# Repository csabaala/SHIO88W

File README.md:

# SHIO88W

ESP32 based DIN rail mount IO board.

More [Pictures](/Pictures#assembled-boards) and [Video](https://youtu.be/fpFCvI0ayuA) of the assembled board and extensions.

Example [ESPHome configs](/ESPHome)

## Features

* 12V DC input for powering
* 8 open collector output (50 mA load per channel)
* 8 opto isolated input
* LEDs for output and input status
* 1 sensor input (ds18b20, dht)
* 14 pin IDC connector for direct GPIO access

View [3D model](https://3dviewer.net/#model=https://dl.dropbox.com/scl/fi/ps5aiib8u3sv6k7nb4t2t/SHIO88W.wrl?rlkey=a4zxlte14uyzpbyriw4eh9wyb&st=gwqd6p7e&dl=0)

## Extensions

### SHADRS485

Extension board mountable top of the SHIO88W board.

* Sockets and breakout for 2 ADS1115 AD converter
* On board voltage dividers for each channel
* RS-485 interface

View [3D model](https://3dviewer.net/#model=https://dl.dropbox.com/scl/fi/sx0bww4iqjbbnxwdh6ggv/SHADRS485.wrl?rlkey=c4fh2khc0jtckmeib4782orl5&st=69d7faog&dl=0)

### SHHMI

Control interface for SHIO88W.

* PCB for 128x64 OLED display and control buttons. Fits the 0.96 and 1.3 inch OLED versions.
* Mountable top of the SHADRS485 board

View [3D model](https://3dviewer.net/#model=https://dl.dropbox.com/scl/fi/2z42lx2431tqztieb8168/SHHMI.wrl?rlkey=yz81izeonbwx9g51vw6o6f9bu&st=en7jitjy&dl=0)

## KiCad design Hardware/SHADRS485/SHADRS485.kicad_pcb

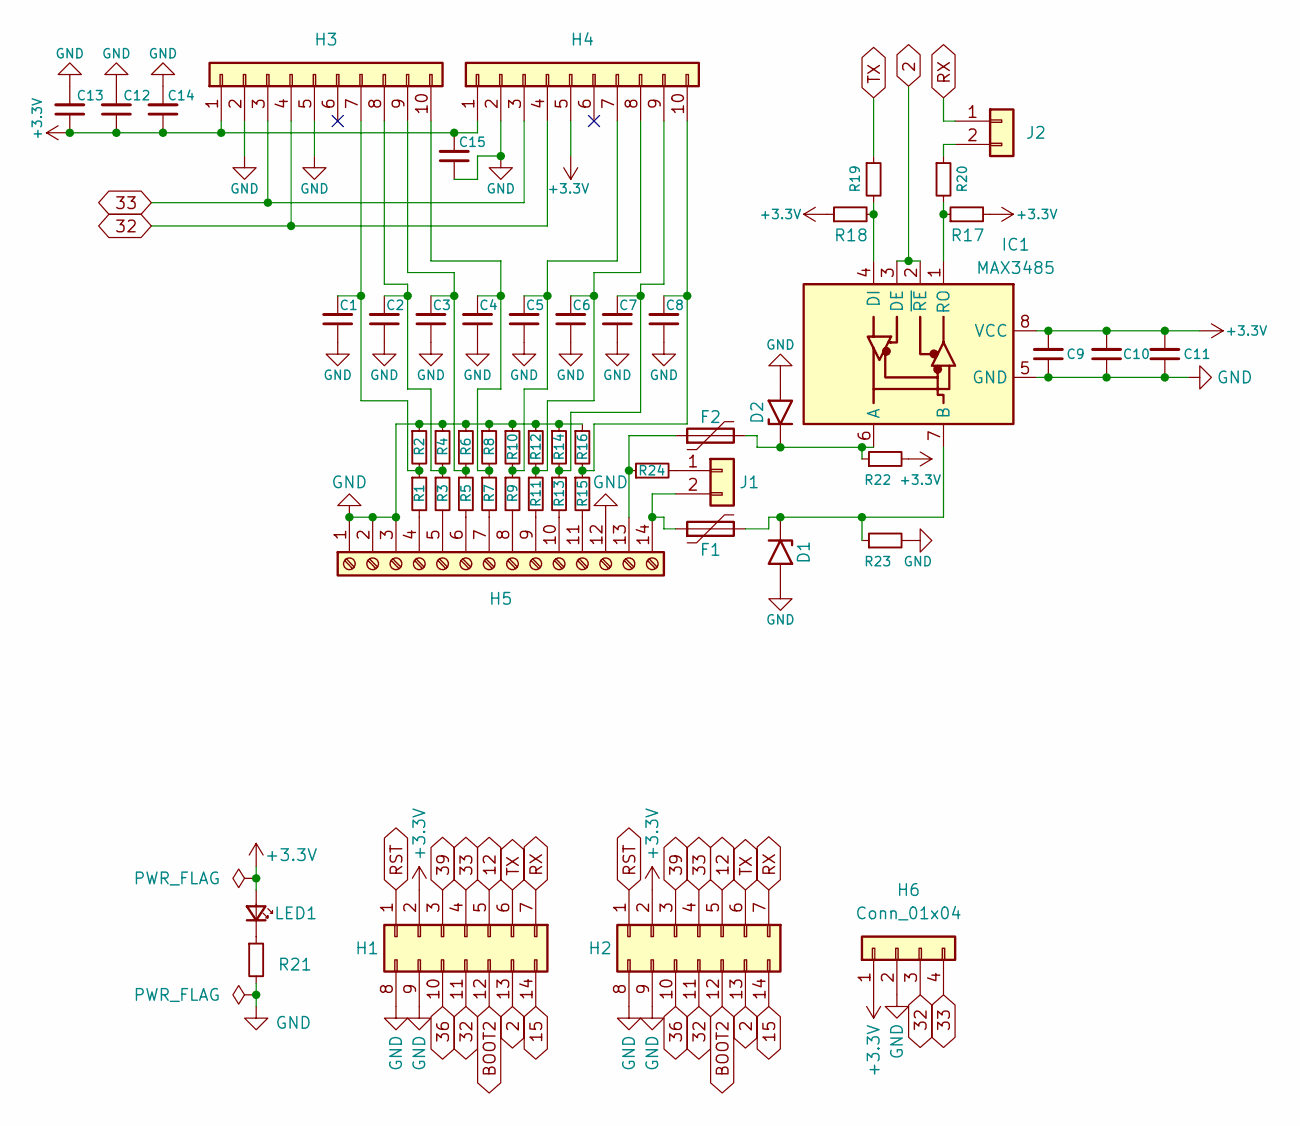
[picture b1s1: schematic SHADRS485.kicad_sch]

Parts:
C1, C2, C3, C4, C5, C6, C7, C8, C9, C10, C14, C15: C_Small; C_0805_2012Metric_Pad1.18x1.45mm_HandSolder; LCSC C49678
C11, C12, C13: C_Small; C_1206_3216Metric_Pad1.33x1.80mm_HandSolder; LCSC C50254
D1, D2: SMBJ12CA; D_SMB; LCSC C353397
F1, F2: Polyfuse; Fuse_1206_3216Metric_Pad1.42x1.75mm_HandSolder; LCSC C2830235
H1: Conn_02x07_Top_Bottom; IDC-Header_2x07_P2.54mm_Vertical
H2: Conn_02x07_Top_Bottom; PinSocket_2x07_P2.54mm_Vertical
H3, H4: Conn_01x10; PinSocket_1x10_P2.54mm_Vertical
H5: Screw_Terminal_01x14; MSTB 2,5 14-G-5,08
H6: Conn_01x04; JST_EH_S4B-EH_1x04_P2.50mm_Horizontal
IC1: MAX3485; SOIC-8_3.9x4.9mm_P1.27mm; LCSC C9943
J1, J2: Conn_01x02; PinHeader_1x02_P2.54mm_Vertical
LED1: LED_Small; LED_0805_2012Metric_Pad1.15x1.40mm_HandSolder; LCSC C2296
R1, R2, R3, R4, R5, R6, R7, R8, R9, R10, R11, R12, R13, R14, R15, R16: R_Small; R_Axial_DIN0204_L3.6mm_D1.6mm_P5.08mm_Horizontal
R17, R18, R21: R_Small; R_0805_2012Metric_Pad1.20x1.40mm_HandSolder; LCSC C17414
R19, R20: R_Small; R_0805_2012Metric_Pad1.20x1.40mm_HandSolder; LCSC C17408
R22, R23: R_Small; R_0805_2012Metric_Pad1.20x1.40mm_HandSolder
R24: R_Small; R_0805_2012Metric_Pad1.20x1.40mm_HandSolder; LCSC C17437

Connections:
2: H1.13, H2.13, IC1.2 (~RE), IC1.3 (DE)
12: H1.5, H2.5
15: H1.14, H2.14
32: H1.11, H2.11, H3.4, H4.4, H6.3
33: H1.4, H2.4, H3.3, H4.3, H6.4
36: H1.10, H2.10
39: H1.3, H2.3
+3.3V: C9.2, C10.2, C11.2, C12.1, C13.1, C14.1, C15.2, H1.2, H2.2, H3.1, H4.1, H4.5, H6.1, IC1.8 (VCC), LED1.2 (A), R17.2, R18.1, R22.2
BOOT2: H1.12, H2.12
GND: C1.1, C2.1, C3.1, C4.1, C5.1, C6.1, C7.1, C8.1, C9.1, C10.1, C11.1, C12.2, C13.2, C14.2, C15.1, D1.2 (A2), D2.2 (A2), H1.8, H1.9, H2.8, H2.9, H3.2, H3.5, H4.2, H5.1, H5.2, H5.3, H5.12, H6.2, IC1.5 (GND), R2.1, R4.1, R6.1, R8.1, R10.1, R12.1, R14.1, R16.1, R21.2, R23.2
unnamed: D1.1 (A1), F1.2, IC1.7 (B), R23.1
unnamed: D2.1 (A1), F2.2, IC1.6 (A), R22.1
unnamed: C1.2, H3.7, R1.1, R2.2
unnamed: C2.2, H3.8, R3.1, R4.2
unnamed: C3.2, H3.9, R5.1, R6.2
unnamed: C4.2, H3.10, R7.1, R8.2
unnamed: C5.2, H4.7, R9.1, R10.2
unnamed: C6.2, H4.8, R11.1, R12.2
unnamed: C7.2, H4.9, R13.1, R14.2
unnamed: C8.2, H4.10, R15.1, R16.2
unnamed: H5.4, R1.2
unnamed: H5.5, R3.2
unnamed: H5.6, R5.2
unnamed: H5.7, R7.2
unnamed: H5.8, R9.2
unnamed: H5.9, R11.2
unnamed: H5.10, R13.2
unnamed: H5.11, R15.2
unnamed: F2.1, H5.13, R24.1
unnamed: F1.1, H5.14, J1.2
unnamed: IC1.4 (DI), R18.2, R19.2
unnamed: IC1.1 (RO), R17.1, R20.2
unnamed: J1.1, R24.2
unnamed: J2.2, R20.1
unnamed: LED1.1 (K), R21.1
RST: H1.1, H2.1
RX: H1.7, H2.7, J2.1
TX: H1.6, H2.6, R19.1

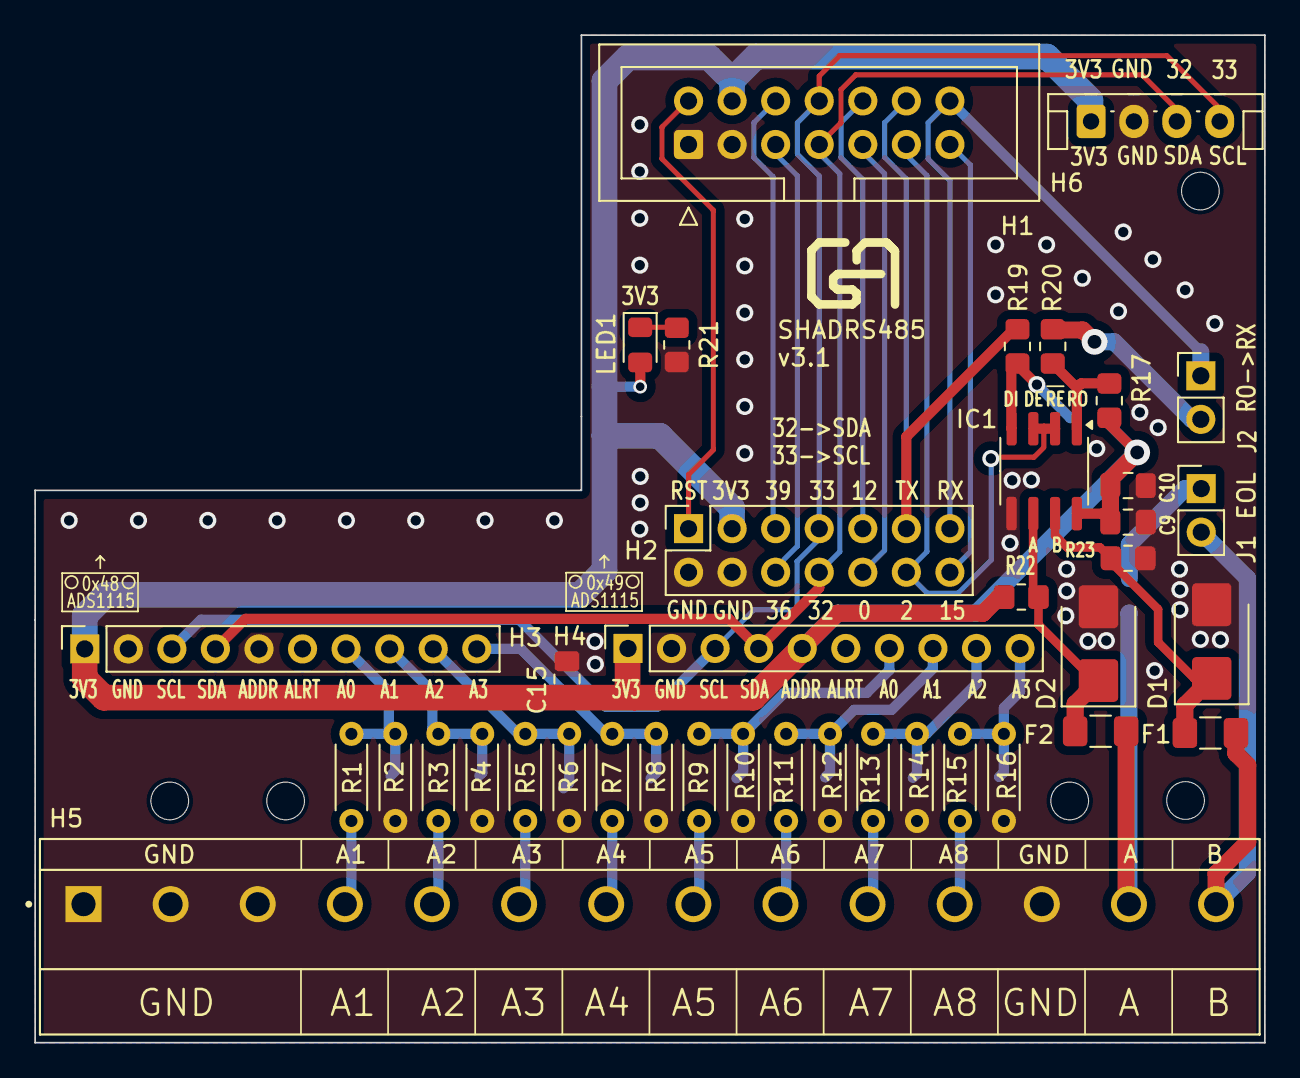
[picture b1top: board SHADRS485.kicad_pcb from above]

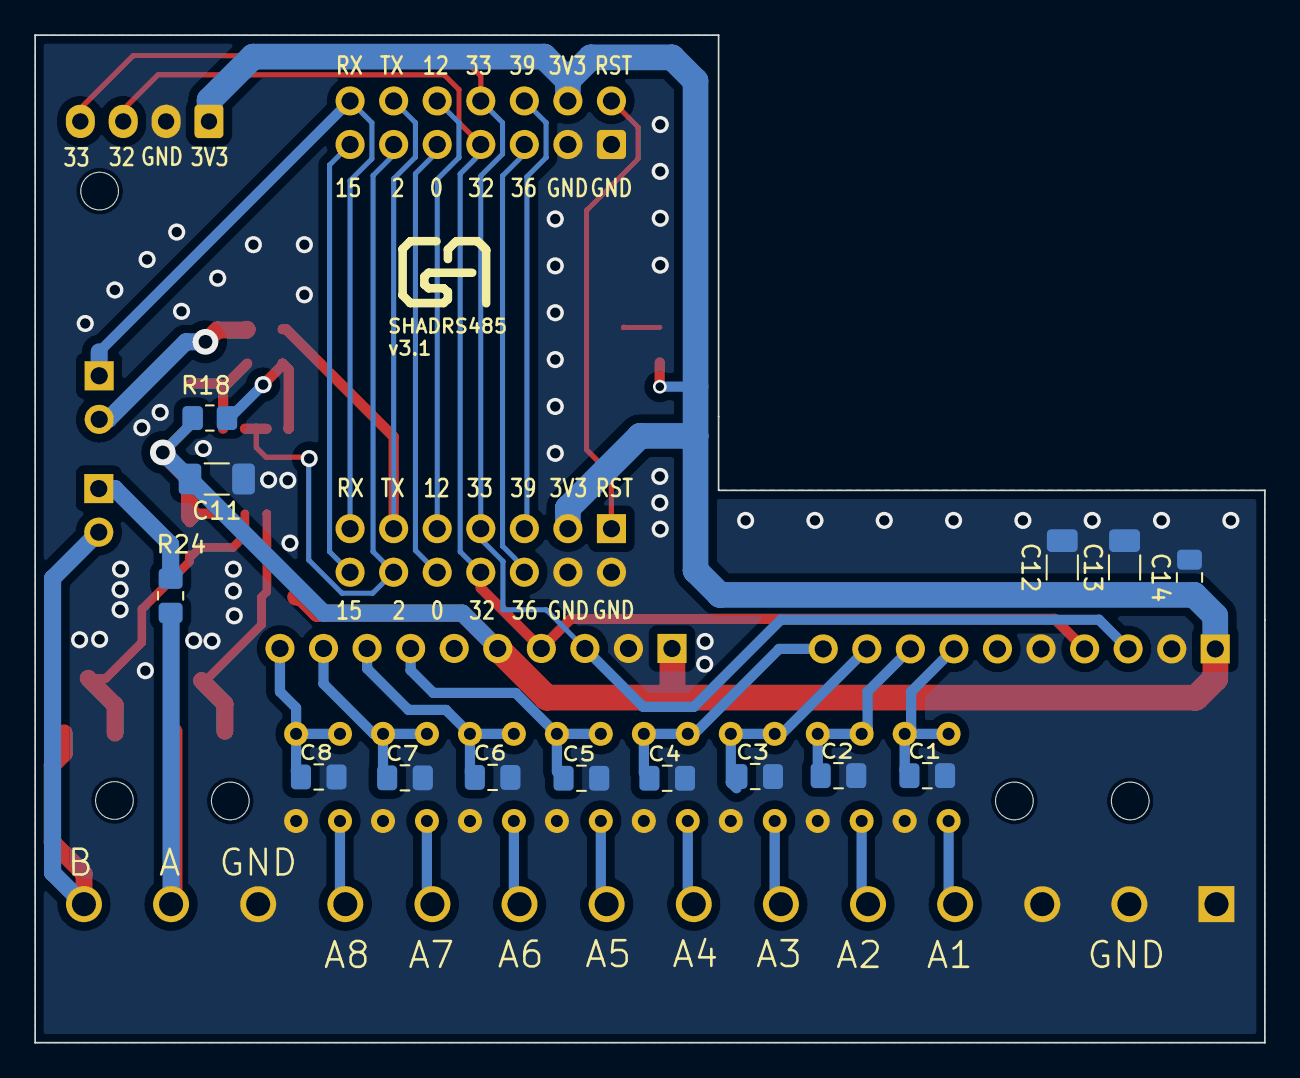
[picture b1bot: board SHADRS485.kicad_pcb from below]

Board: 2 copper layers, 71.7 x 58.8 mm, 53 parts (14 on the bottom side), 38 nets.

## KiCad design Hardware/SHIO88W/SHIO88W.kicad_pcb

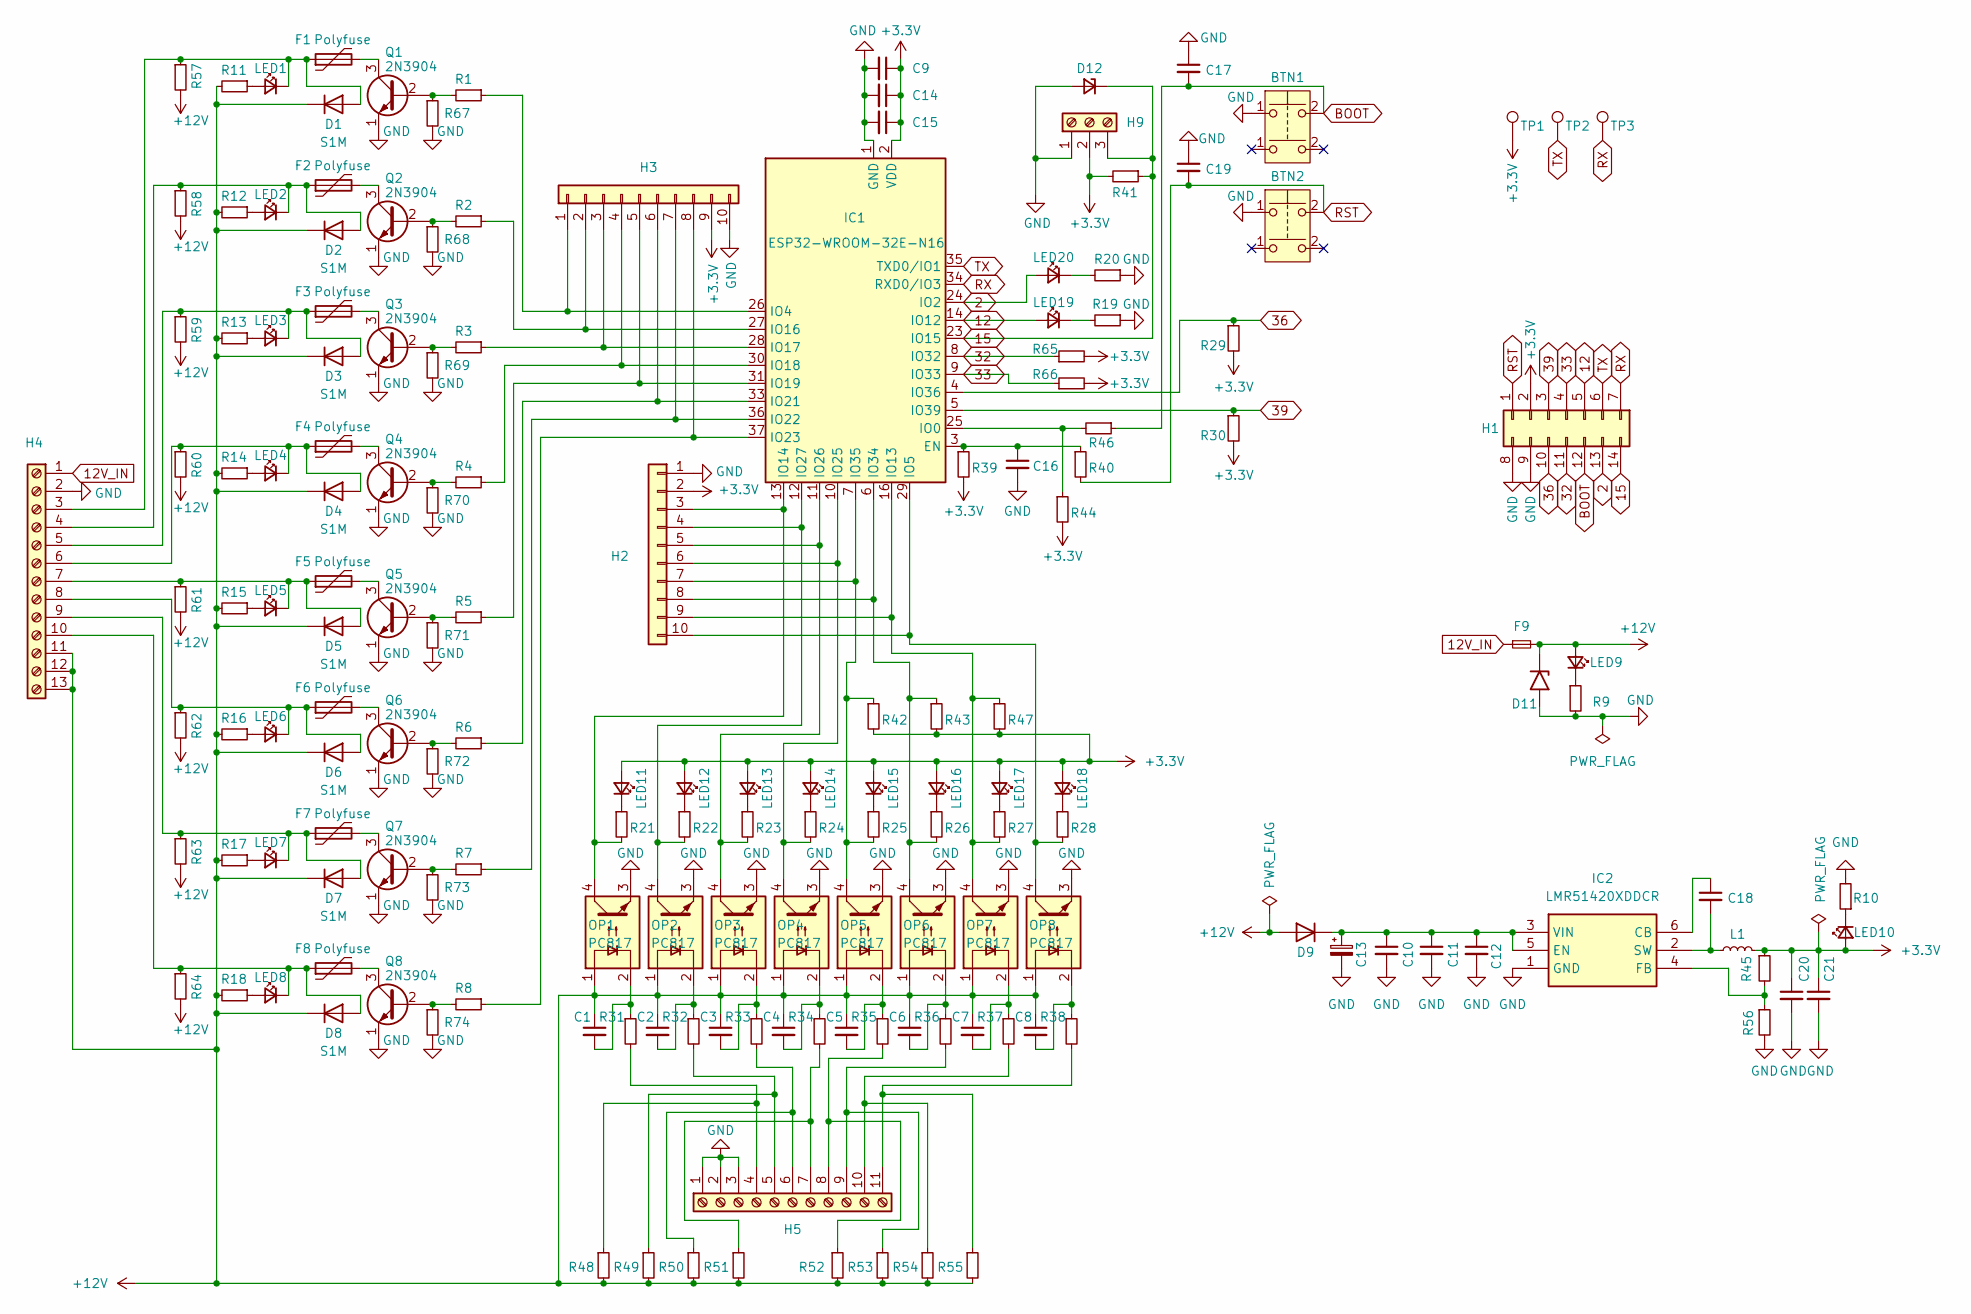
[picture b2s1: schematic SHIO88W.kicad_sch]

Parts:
BTN1, BTN2: SW_Push_Dual; SW_Push_1P1T_XKB_TS-1187A; LCSC C318884
C1, C2, C3, C4, C5, C6, C7, C8: C_Small; C_0805_2012Metric_Pad1.18x1.45mm_HandSolder; LCSC C1710
C9, C14, C20, C21: C_Small; C_1206_3216Metric_Pad1.33x1.80mm_HandSolder; LCSC C12891
C10, C11: C_Small; C_1206_3216Metric_Pad1.33x1.80mm_HandSolder; LCSC C13585
C12: C_Small; C_1206_3216Metric_Pad1.33x1.80mm_HandSolder; LCSC C50254
C13: C_Polarized_Small; CP_Radial_D10.0mm_P5.00mm
C15, C17, C18, C19: C_Small; C_0805_2012Metric_Pad1.18x1.45mm_HandSolder; LCSC C49678
C16: C_Small; C_0805_2012Metric_Pad1.18x1.45mm_HandSolder; LCSC C28323
D1, D2, D3, D4, D5, D6, D7, D8: S1M; D_SMA
D9: S1M; D_SMA; LCSC C412437
D11: SM6T18A; D_SMB; LCSC C353369
D12: D_Zener_Small; Nexperia_CFP3_SOD-123W; LCSC C2903912
F1, F2, F3, F4, F5, F6, F7, F8: Polyfuse; Fuse_1206_3216Metric_Pad1.42x1.75mm_HandSolder
F9: Fuse_Small; FUSE_holder
H1: Conn_02x07_Top_Bottom; IDC-Header_2x07_P2.54mm_Vertical
H2, H3: Conn_01x10; PinHeader_1x10_P2.54mm_Vertical
H4: Screw_Terminal_01x13; TerminalBlock_MSTBV 2,513-G-5,08
H5: Screw_Terminal_01x11; TerminalBlock_MSTB 2,511-G-5,08
H9: Screw_Terminal_01x03; TerminalBlock_MSTB 2,5 3-G-5,08
IC1: ESP32-WROOM-32E-N16; ESP32-WROOM-32E; JLCPCB Rotation Offset 270
IC2: LMR51420XDDCR; LMR51420; Mouser Part Number 595-LMR51420XDDCR
L1: L_Small; L_Chilisin_BMRx00060630; LCSC C497872
LED1, LED2, LED3, LED4, LED5, LED6, LED7, LED8, LED11, LED12, LED13, LED14, LED15, LED16, LED17, LED18, LED19: LED_Small; LED_0805_2012Metric_Pad1.15x1.40mm_HandSolder; LCSC C84256
LED9, LED10: LED_Small; LED_0805_2012Metric_Pad1.15x1.40mm_HandSolder; LCSC C2296
LED20: LED_Small; LED_0805_2012Metric_Pad1.15x1.40mm_HandSolder; LCSC C2297
OP1, OP2, OP3, OP4, OP5, OP6, OP7, OP8: PC817; PC817_custom
Q1, Q2, Q3, Q4, Q5, Q6, Q7, Q8: 2N3904; TO-92_HandSolder
R1, R2, R3, R4, R5, R6, R7, R8: R_Small; R_0805_2012Metric_Pad1.20x1.40mm_HandSolder; LCSC C17513
R9, R11, R12, R13, R14, R15, R16, R17, R18, R20, R29, R30, R39, R42, R43, R44, R47: R_Small; R_0805_2012Metric_Pad1.20x1.40mm_HandSolder; LCSC C17414
R10, R19, R21, R22, R23, R24, R25, R26, R27, R28, R31, R32, R33, R34, R35, R36, R37, R38: R_Small; R_0805_2012Metric_Pad1.20x1.40mm_HandSolder; LCSC C17520
R40, R46: R_Small; R_0805_2012Metric_Pad1.20x1.40mm_HandSolder; LCSC C17710
R41: R_Small; R_0805_2012Metric_Pad1.20x1.40mm_HandSolder; LCSC C17673
R45, R48, R49, R50, R51, R52, R53, R54, R55, R56, R57, R58, R59, R60, R61, R62, R63, R64, R65, R66, R67, R68, R69, R70, R71, R72, R73, R74: R_Small; R_0805_2012Metric_Pad1.20x1.40mm_HandSolder
TP1, TP2, TP3: TestPoint; TestPoint_Pad_D2.0mm_custom

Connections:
2: H1.13, IC1.24 (IO2), LED20.2 (A)
12: H1.5, IC1.14 (IO12), LED19.2 (A)
12V_IN: F9.1, H4.1
15: D12.1 (K), H1.14, H9.3, IC1.23 (IO15), R41.1
32: H1.11, IC1.8 (IO32), R65.1
33: H1.4, IC1.9 (IO33), R66.1
36: H1.10, IC1.4 (IO36), R29.1
39: H1.3, IC1.5 (IO39), R30.1
+3.3V: C9.1, C14.1, C15.1, C20.1, C21.1, H1.2, H2.2, H3.9, H9.2, IC1.2 (VDD), L1.2, LED10.2 (A), LED11.2 (A), LED12.2 (A), LED13.2 (A), LED14.2 (A), LED15.2 (A), LED16.2 (A), LED17.2 (A), LED18.2 (A), R29.2, R30.2, R39.2, R41.2, R42.2, R43.2, R44.2, R45.1, R47.2, R65.2, R66.2, TP1.1
+12V: C1.1, C2.1, C3.1, C4.1, C5.1, C6.1, C7.1, C8.1, D1.1 (K), D2.1 (K), D3.1 (K), D4.1 (K), D5.1 (K), D6.1 (K), D7.1 (K), D8.1 (K), D9.2 (A), D11.1 (A1), F9.2, H4.11, H4.12, H4.13, LED9.2 (A), OP1.1, OP2.1, OP3.1, OP4.1, OP5.1, OP6.1, OP7.1, OP8.1, R11.2, R12.2, R13.2, R14.2, R15.2, R16.2, R17.2, R18.2, R48.2, R49.2, R50.2, R51.2, R52.2, R53.2, R54.2, R55.2, R57.2, R58.2, R59.2, R60.2, R61.2, R62.2, R63.2, R64.2
BOOT: BTN1.2, C17.2, H1.12, R46.1
GND: BTN1.1, BTN2.1, C9.2, C10.2, C11.2, C12.2, C13.2, C14.2, C15.2, C16.2, C17.1, C19.1, C20.2, C21.2, D11.2 (A2), D12.2 (A), H1.8, H1.9, H2.1, H3.10, H4.2, H5.1, H5.2, H5.3, H9.1, IC1.1 (GND), IC1.15 (GND), IC1.38 (GND), IC1.39 (GND), IC2.1 (GND), OP1.3, OP2.3, OP3.3, OP4.3, OP5.3, OP6.3, OP7.3, OP8.3, Q1.1 (E), Q2.1 (E), Q3.1 (E), Q4.1 (E), Q5.1 (E), Q6.1 (E), Q7.1 (E), Q8.1 (E), R9.2, R10.2, R19.1, R20.1, R56.2, R67.2, R68.2, R69.2, R70.2, R71.2, R72.2, R73.2, R74.2
unnamed: C1.2, OP1.2, R31.1
unnamed: C2.2, OP2.2, R32.1
unnamed: C3.2, OP3.2, R33.1
unnamed: C4.2, OP4.2, R34.1
unnamed: C5.2, OP5.2, R35.1
unnamed: C6.2, OP6.2, R36.1
unnamed: C7.2, OP7.2, R37.1
unnamed: C8.2, OP8.2, R38.1
unnamed: D1.2 (A), F1.1, H4.3, LED1.1 (K), R57.1
unnamed: D2.2 (A), F2.1, H4.4, LED2.1 (K), R58.1
unnamed: D3.2 (A), F3.1, H4.5, LED3.1 (K), R59.1
unnamed: D4.2 (A), F4.1, H4.6, LED4.1 (K), R60.1
unnamed: D5.2 (A), F5.1, H4.7, LED5.1 (K), R61.1
unnamed: D6.2 (A), F6.1, H4.8, LED6.1 (K), R62.1
unnamed: D7.2 (A), F7.1, H4.9, LED7.1 (K), R63.1
unnamed: D8.2 (A), F8.1, H4.10, LED8.1 (K), R64.1
unnamed: C10.1, C11.1, C12.1, C13.1, D9.1 (K), IC2.3 (VIN), IC2.5 (EN)
unnamed: H2.3, IC1.13 (IO14), OP1.4, R21.2
unnamed: H2.4, IC1.12 (IO27), OP2.4, R22.2
unnamed: H2.5, IC1.11 (IO26), OP3.4, R23.2
unnamed: H2.6, IC1.10 (IO25), OP4.4, R24.2
unnamed: H2.7, IC1.7 (IO35), OP5.4, R25.2, R42.1
unnamed: H2.8, IC1.6 (IO34), OP6.4, R26.2, R43.1
unnamed: H2.9, IC1.16 (IO13), OP7.4, R27.2, R47.1
unnamed: H2.10, IC1.29 (IO5), OP8.4, R28.2
unnamed: H3.1, IC1.26 (IO4), R1.1
unnamed: H3.2, IC1.27 (IO16), R2.1
unnamed: H3.3, IC1.28 (IO17), R3.1
unnamed: H3.4, IC1.30 (IO18), R4.1
unnamed: H3.5, IC1.31 (IO19), R5.1
unnamed: H3.6, IC1.33 (IO21), R6.1
unnamed: H3.7, IC1.36 (IO22), R7.1
unnamed: H3.8, IC1.37 (IO23), R8.1
unnamed: H5.4, R31.2, R48.1
unnamed: H5.5, R32.2, R49.1
unnamed: H5.6, R33.2, R50.1
unnamed: H5.7, R34.2, R51.1
unnamed: H5.8, R35.2, R52.1
unnamed: H5.9, R36.2, R53.1
unnamed: H5.10, R37.2, R54.1
unnamed: H5.11, R38.2, R55.1
unnamed: C16.1, IC1.3 (EN), R39.1, R40.1
unnamed: IC1.25 (IO0), R44.1, R46.2
unnamed: C18.1, IC2.6 (CB)
unnamed: IC2.4 (FB), R45.2, R56.1
unnamed: C18.2, IC2.2 (SW), L1.1
unnamed: LED1.2 (A), R11.1
unnamed: LED2.2 (A), R12.1
unnamed: LED3.2 (A), R13.1
unnamed: LED4.2 (A), R14.1
unnamed: LED5.2 (A), R15.1
unnamed: LED6.2 (A), R16.1
unnamed: LED7.2 (A), R17.1
unnamed: LED8.2 (A), R18.1
unnamed: LED9.1 (K), R9.1
unnamed: LED10.1 (K), R10.1
unnamed: LED11.1 (K), R21.1
unnamed: LED12.1 (K), R22.1
unnamed: LED13.1 (K), R23.1
unnamed: LED14.1 (K), R24.1
unnamed: LED15.1 (K), R25.1
unnamed: LED16.1 (K), R26.1
unnamed: LED17.1 (K), R27.1
unnamed: LED18.1 (K), R28.1
unnamed: LED19.1 (K), R19.2
unnamed: LED20.1 (K), R20.2
unnamed: Q1.2 (B), R1.2, R67.1
unnamed: F1.2, Q1.3 (C)
unnamed: Q2.2 (B), R2.2, R68.1
unnamed: F2.2, Q2.3 (C)
unnamed: Q3.2 (B), R3.2, R69.1
unnamed: F3.2, Q3.3 (C)
unnamed: Q4.2 (B), R4.2, R70.1
unnamed: F4.2, Q4.3 (C)
unnamed: Q5.2 (B), R5.2, R71.1
unnamed: F5.2, Q5.3 (C)
unnamed: Q6.2 (B), R6.2, R72.1
unnamed: F6.2, Q6.3 (C)
unnamed: Q7.2 (B), R7.2, R73.1
unnamed: F7.2, Q7.3 (C)
unnamed: Q8.2 (B), R8.2, R74.1
unnamed: F8.2, Q8.3 (C)
RST: BTN2.2, C19.2, H1.1, R40.2
RX: H1.7, IC1.34 (RXD0/IO3), TP3.1
TX: H1.6, IC1.35 (TXD0/IO1), TP2.1

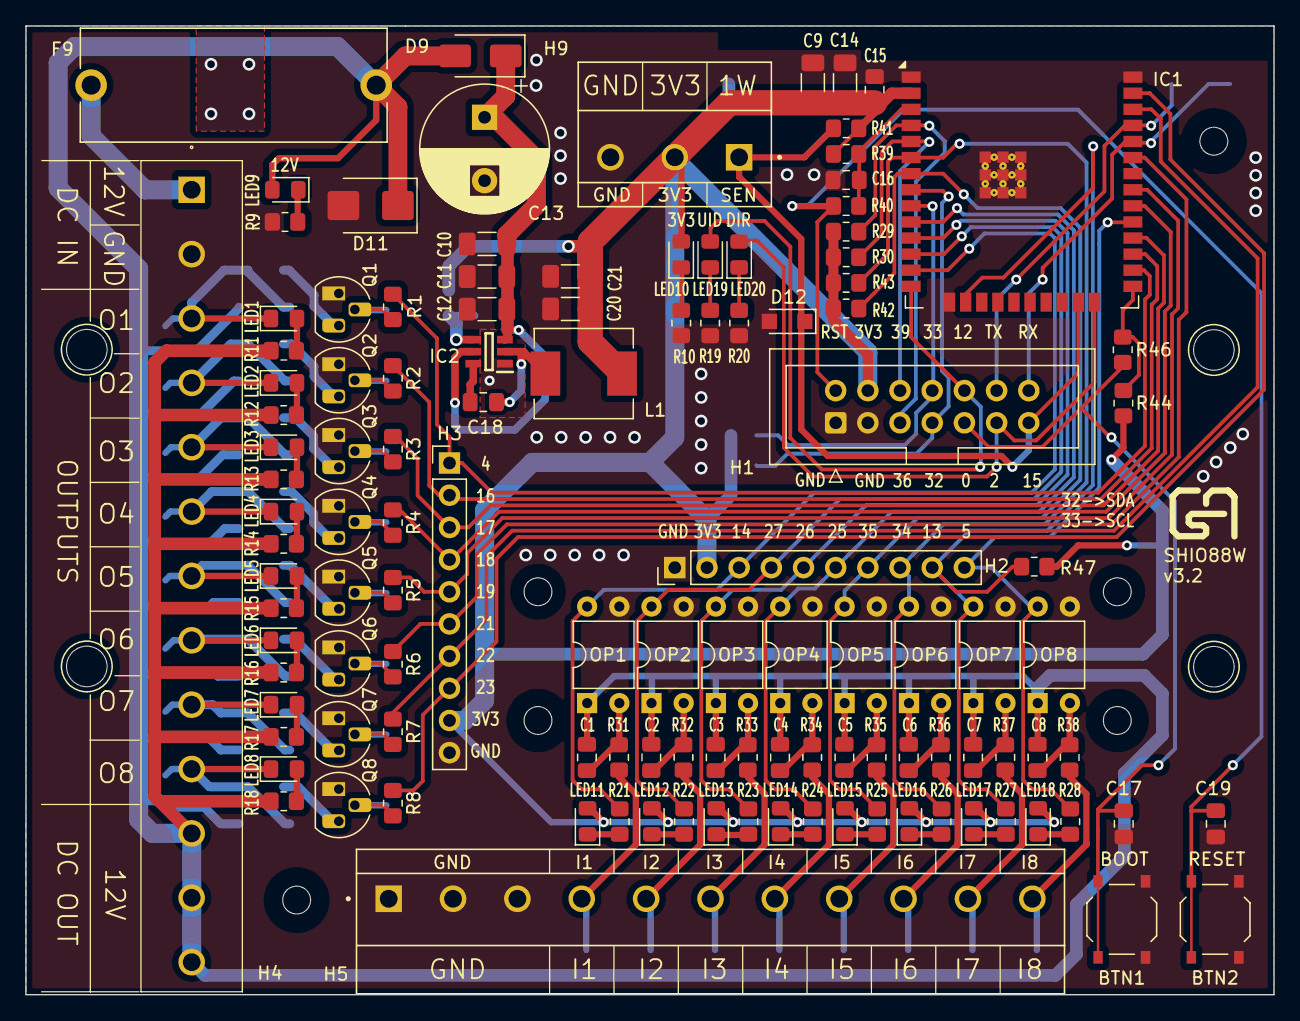
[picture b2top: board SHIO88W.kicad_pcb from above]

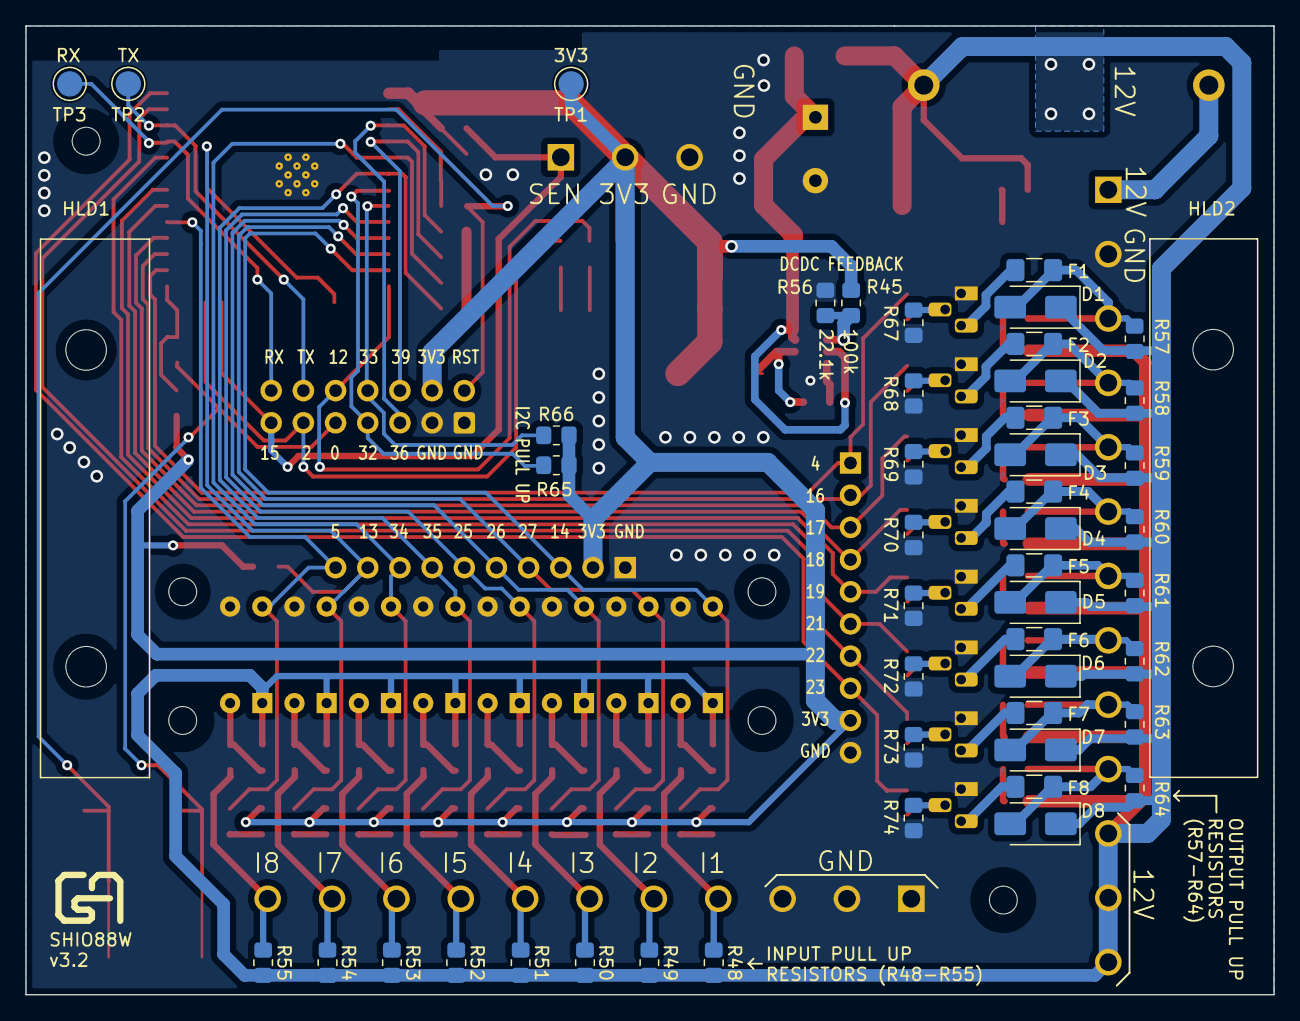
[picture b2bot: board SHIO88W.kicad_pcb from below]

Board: 2 copper layers, 98.5 x 76.5 mm, 167 parts (47 on the bottom side), 97 nets.

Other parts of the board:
HLD1, HLD2: DINRailAdapter_3xM3_PhoenixContact_1201578

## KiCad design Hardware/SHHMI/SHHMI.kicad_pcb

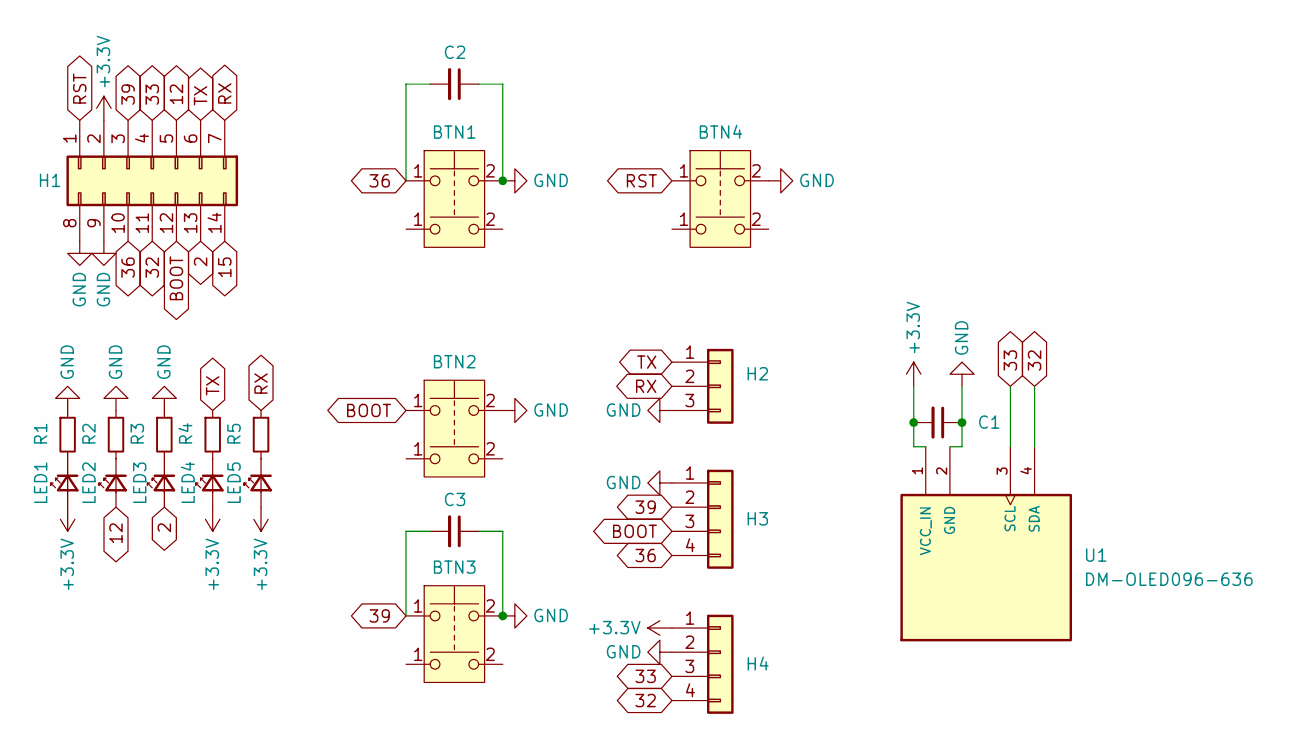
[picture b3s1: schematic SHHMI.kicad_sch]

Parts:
BTN1, BTN2, BTN3, BTN4: SW_Push_Dual; SW_SPST_PTS645_handsolder
C1, C2, C3: C_Small; C_0805_2012Metric_Pad1.18x1.45mm_HandSolder; LCSC C49678
H1: Conn_02x07_Top_Bottom; PinSocket_2x07_P2.54mm_Vertical
H2: Conn_01x03; PinHeader_1x03_P2.54mm_Vertical
H3, H4: Conn_01x04; PinHeader_1x04_P2.54mm_Vertical
LED1, LED5: LED_Small; LED_0805_2012Metric_Pad1.15x1.40mm_HandSolder; LCSC C2296
LED2: LED_Small; LED_0805_2012Metric_Pad1.15x1.40mm_HandSolder; LCSC C84256
LED3, LED4: LED_Small; LED_0805_2012Metric_Pad1.15x1.40mm_HandSolder; LCSC C2297
R1, R2, R3, R4, R5: R_Small; R_0805_2012Metric_Pad1.20x1.40mm_HandSolder; LCSC C17414
U1: DM-OLED096-636; display_oled_128x64_i2c; PARTREV 2018-09-10

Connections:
2: H1.13, LED3.2 (A)
12: H1.5, LED2.2 (A)
15: H1.14
32: H1.11, H4.4, U1.4 (SDA)
33: H1.4, H4.3, U1.3 (SCL)
36: BTN1.1, C2.2, H1.10, H3.4
39: BTN3.1, C3.2, H1.3, H3.2
+3.3V: C1.2, H1.2, H4.1, LED1.2 (A), LED4.2 (A), LED5.2 (A), U1.1 (VCC_IN)
BOOT: BTN2.1, H1.12, H3.3
GND: BTN1.2, BTN2.2, BTN3.2, BTN4.2, C1.1, C2.1, C3.1, H1.8, H1.9, H2.3, H3.1, H4.2, R1.1, R2.1, R3.1, U1.2 (GND)
unnamed: LED1.1 (K), R1.2
unnamed: LED2.1 (K), R2.2
unnamed: LED3.1 (K), R3.2
unnamed: LED4.1 (K), R4.2
unnamed: LED5.1 (K), R5.2
RST: BTN4.1, H1.1
RX: H1.7, H2.2, R5.1
TX: H1.6, H2.1, R4.1

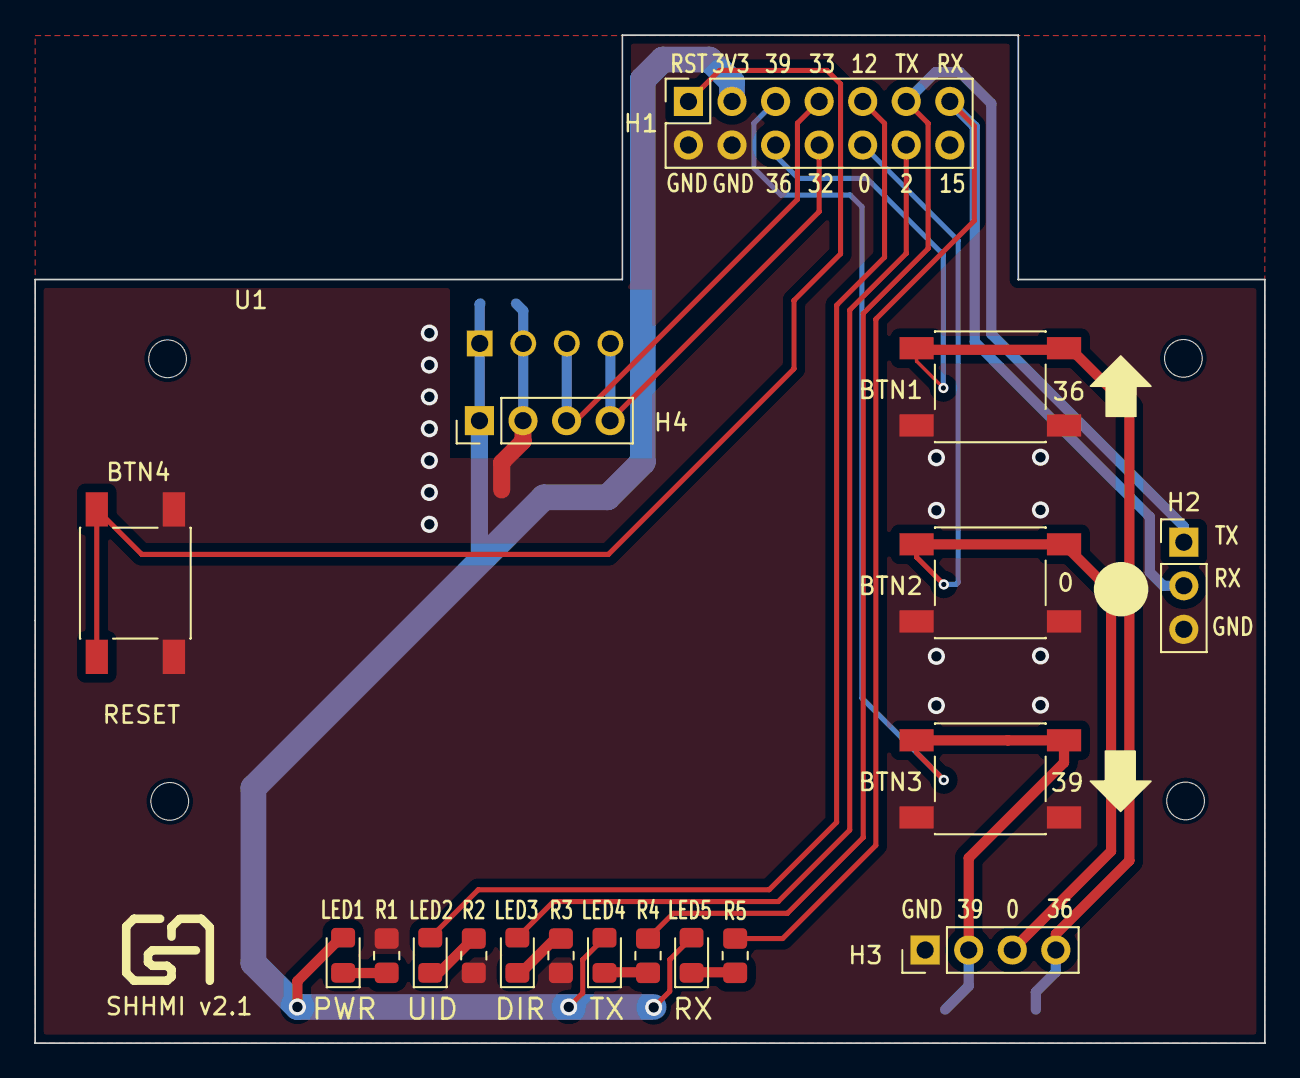
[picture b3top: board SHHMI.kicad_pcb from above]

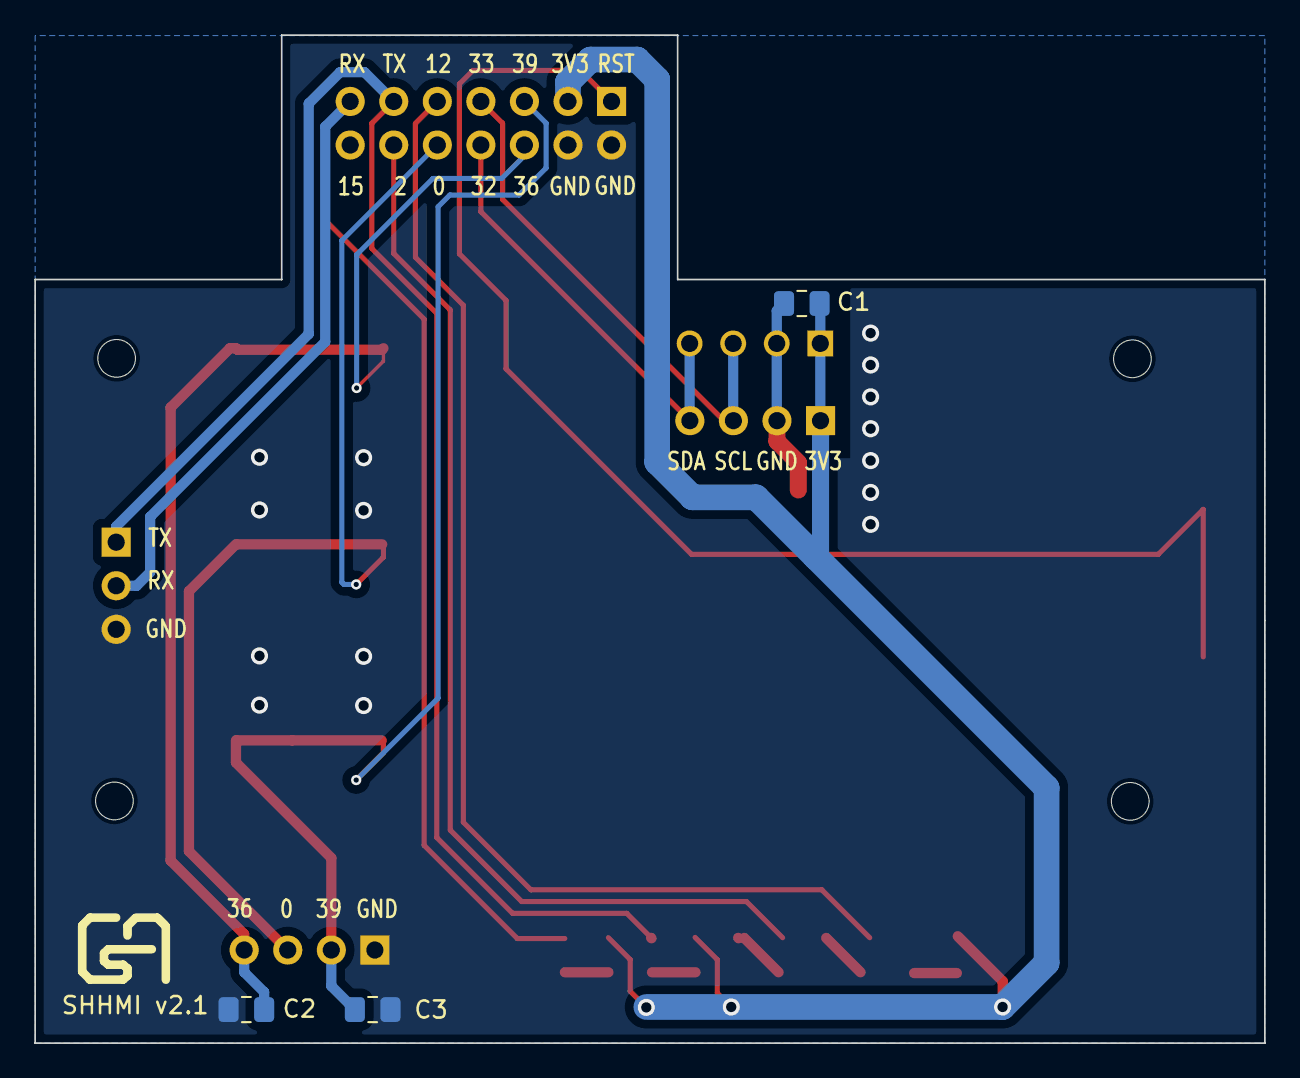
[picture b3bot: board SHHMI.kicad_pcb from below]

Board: 2 copper layers, 71.7 x 58.8 mm, 22 parts (3 on the bottom side), 17 nets.

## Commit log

2025-04-06 updated pictures readme
2025-04-07 hardware folder added
2025-06-09 added esphome configs
2025-06-09 Create LICENSE
2026-02-15 added fp-lib-table
